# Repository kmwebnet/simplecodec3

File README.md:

# Audio input/output board for Raspberry Pi, Jetson Nano (PCM5102A+PCM1808)

This project related to my article.
[Creating an audio input/output board for Raspberry Pi, Jetson Nano (PCM5102A+PCM1808)](https://kentaromitsuyasu.medium.com/creating-an-audio-input-output-board-for-raspberry-pi-jetson-nano-pcm5102a-pcm1808-e3e6f3ad0834)  

In Japanese, [Raspberry Pi, Jetson Nano向けオーディオ入出力ボードの作成(PCM5102A+PCM1808編)](https://qiita.com/kmitsu76/items/07b0bea26ad996e16b30)   

# Environment reference 

This project has tested:  
Raspberry pi 3b  
Raspberry pi 4  
Jetson Nano A02  
Jetson Nano B01  

# Usage

you need to check the driver install instruction for:   
  
[Raspberry pi](https://kentaromitsuyasu.medium.com/creating-an-audio-input-output-board-for-raspberry-pi-jetson-nano-pcm5102a-pcm1808-e3e6f3ad0834)   
    
[Jetson Nano](https://kentaromitsuyasu.medium.com/creating-an-audio-input-output-board-for-raspberry-pi-jetson-nano-porting-trouble-to-jetson-nano-d4674ec4e48e)   

# Notes
You can ignore ATECC608A I2C pattern if you won't use it.

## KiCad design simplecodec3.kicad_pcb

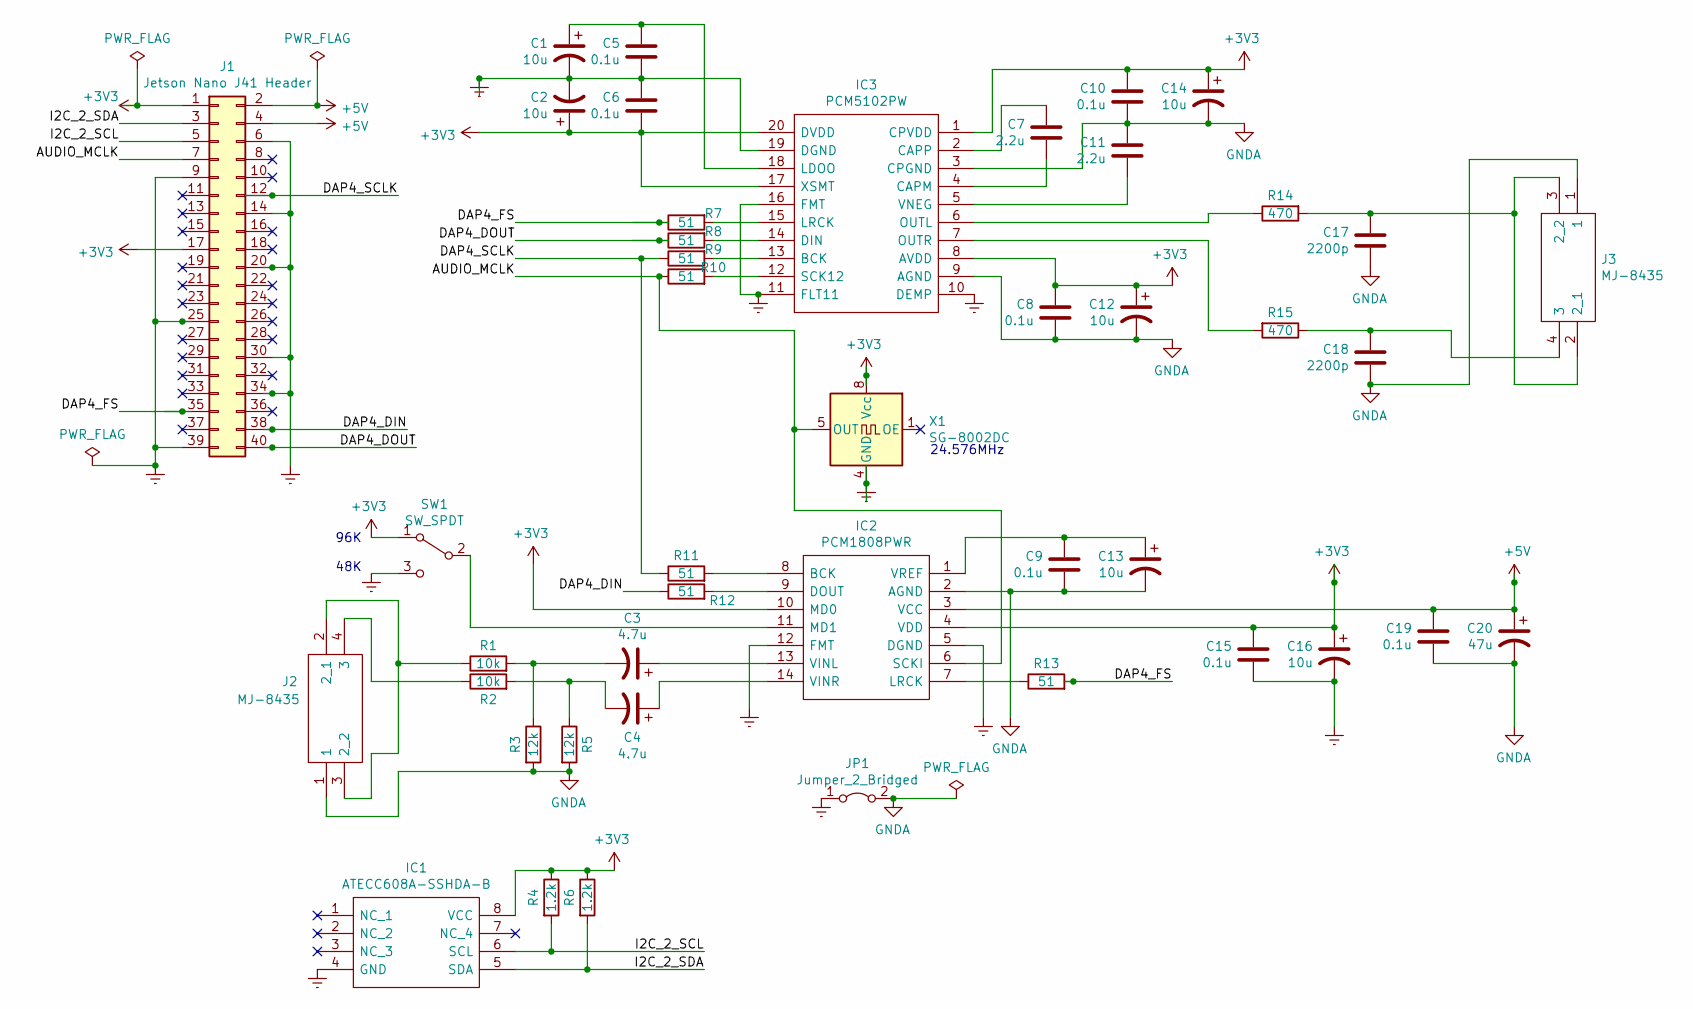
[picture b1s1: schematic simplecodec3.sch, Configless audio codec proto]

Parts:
C1, C2, C12, C13, C14, C16: 10u; C_0603_1608Metric_Pad1.05x0.95mm_HandSolder
C3, C4: 4.7u; C_0603_1608Metric_Pad1.05x0.95mm_HandSolder
C5, C6, C8, C9, C10, C15, C19: 0.1u; C_0603_1608Metric_Pad1.05x0.95mm_HandSolder
C7, C11: 2.2u; C_0402_1005Metric
C17, C18: 2200p; C_Rect_L7.0mm_W3.5mm_P5.00mm
C20: 47u; CP_Radial_D6.3mm_P2.50mm
IC1: ATECC608A-SSHDA-B; SOIC127P600X175-8N; Manufacturer_Part_Number ATECC608A-SSHDA-B; Mouser Part Number 556-ATECC608ASSHDAB
IC2: PCM1808PWR; Manufacturer_Part_Number PCM1808PWR; Mouser Part Number 595-PCM1808PWR
IC3: PCM5102PW; SOP65P640X120-20N; Manufacturer_Part_Number PCM5102PW; Mouser Part Number 595-PCM5102PW
J1: Jetson Nano J41 Header; PinHeader_2x20_P2.54mm_Vertical
J2, J3: MJ-8435; Manufacturer_Part_Number MJ-8435
JP1: Jumper_2_Bridged; SolderJumper-2_P1.3mm_Bridged2Bar_Pad1.0x1.5mm
R1, R2: 10k; R_0603_1608Metric_Pad1.05x0.95mm_HandSolder
R3, R5: 12k; R_0603_1608Metric_Pad1.05x0.95mm_HandSolder
R4, R6: 1.2k; R_0603_1608Metric_Pad1.05x0.95mm_HandSolder
R7, R8, R9, R10, R11, R12, R13: 51; R_0603_1608Metric_Pad1.05x0.95mm_HandSolder
R14, R15: 470; R_0603_1608Metric_Pad1.05x0.95mm_HandSolder
SW1: SW_SPDT; PinHeader_1x03_P2.54mm_Vertical
X1: SG-8002DC; Oscillator_SeikoEpson_SG-8002DC

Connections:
+3V3: C2.1, C6.2, C8.1, C10.1, C12.1, C14.1, C15.1, C16.1, IC1.8 (VCC), IC2.4 (VDD), IC2.10 (MD0), IC3.1 (CPVDD), IC3.8 (AVDD), IC3.17 (XSMT), IC3.20 (DVDD), J1.1, J1.17, R4.1, R6.1, SW1.1 (A), X1.8 (Vcc)
+5V: C19.1, C20.1, IC2.3 (VCC), J1.2, J1.4
/AUDIO_MCLK: IC2.6 (SCKI), J1.7, R10.1, X1.5 (OUT)
/DAP4_DIN: J1.38, R12.1
/DAP4_DOUT: J1.40, R8.1
/DAP4_FS: J1.35, R7.1, R13.2
/DAP4_SCLK: J1.12, R9.1, R11.1
/I2C_2_SCL: IC1.6 (SCL), J1.5, R4.2
/I2C_2_SDA: IC1.5 (SDA), J1.3, R6.2
Earth: C1.2, C2.2, C5.2, C6.1, C15.2, C16.2, IC1.4 (GND), IC2.5 (DGND), IC2.12 (FMT), IC3.10 (DEMP), IC3.11 (FLT11), IC3.16 (FMT), IC3.19 (DGND), J1.6, J1.9, J1.14, J1.20, J1.25, J1.30, J1.34, J1.39, JP1.1 (A), SW1.3 (C), X1.4 (GND)
GNDA: C8.2, C9.2, C10.2, C11.1, C12.2, C13.2, C14.2, C17.2, C18.2, C19.2, C20.2, IC2.2 (AGND), IC3.3 (CPGND), IC3.9 (AGND), J2.1, J3.1, JP1.2 (B), R3.2, R5.2
unnamed: C1.1, C5.1, IC3.18 (LDOO)
unnamed: C3.1, IC2.13 (VINL)
unnamed: C3.2, R1.2, R3.1
unnamed: C4.1, IC2.14 (VINR)
unnamed: C4.2, R2.2, R5.1
unnamed: C7.1, IC3.2 (CAPP)
unnamed: C7.2, IC3.4 (CAPM)
unnamed: C11.2, IC3.5 (VNEG)
unnamed: C9.1, C13.1, IC2.1 (VREF)
unnamed: C17.1, J3.2 (2_1), J3.3 (2_2), R14.2
unnamed: C18.1, J3.4 (3), R15.1
unnamed: IC2.7 (LRCK), R13.1
unnamed: IC2.8 (BCK), R11.2
unnamed: IC2.9 (DOUT), R12.2
unnamed: IC2.11 (MD1), SW1.2 (B)
unnamed: IC3.6 (OUTL), R14.1
unnamed: IC3.7 (OUTR), R15.2
unnamed: IC3.12 (SCK12), R10.2
unnamed: IC3.13 (BCK), R9.2
unnamed: IC3.14 (DIN), R8.2
unnamed: IC3.15 (LRCK), R7.2
unnamed: J2.2 (2_1), J2.3 (2_2), R1.1
unnamed: J2.4 (3), R2.1

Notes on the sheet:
96K 48K
24.576MHz

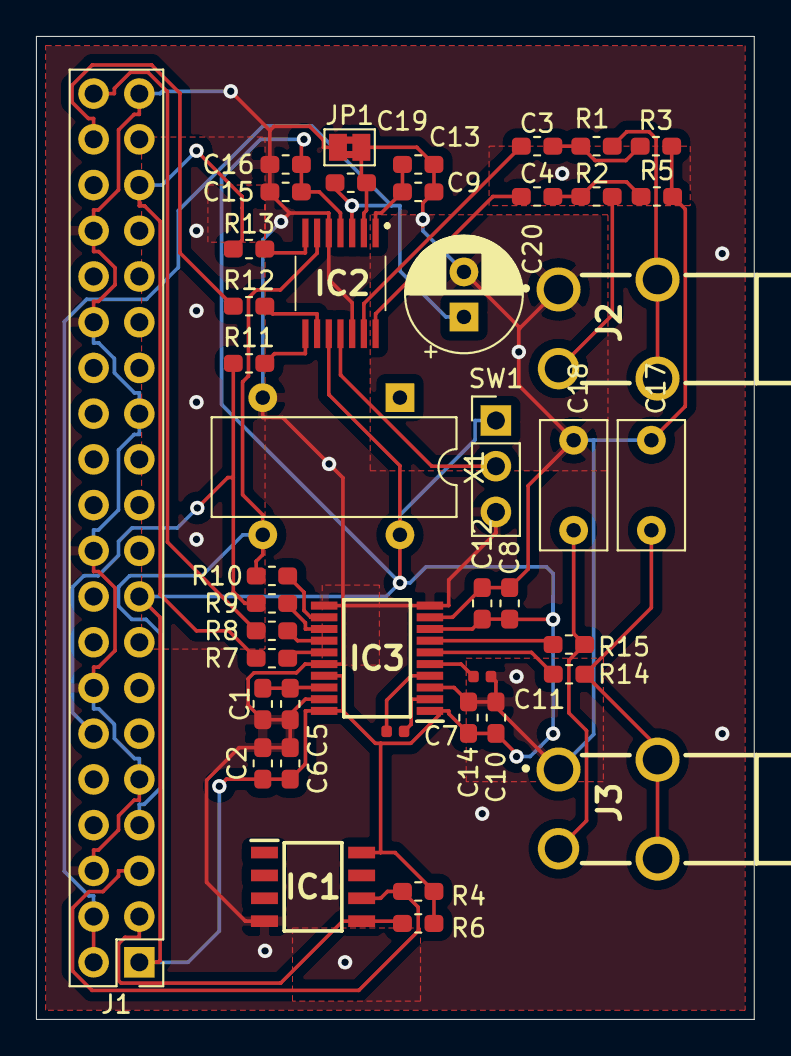
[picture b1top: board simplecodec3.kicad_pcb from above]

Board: 2 copper layers, 39.9 x 54.6 mm, 44 parts (0 on the bottom side), 34 nets.
